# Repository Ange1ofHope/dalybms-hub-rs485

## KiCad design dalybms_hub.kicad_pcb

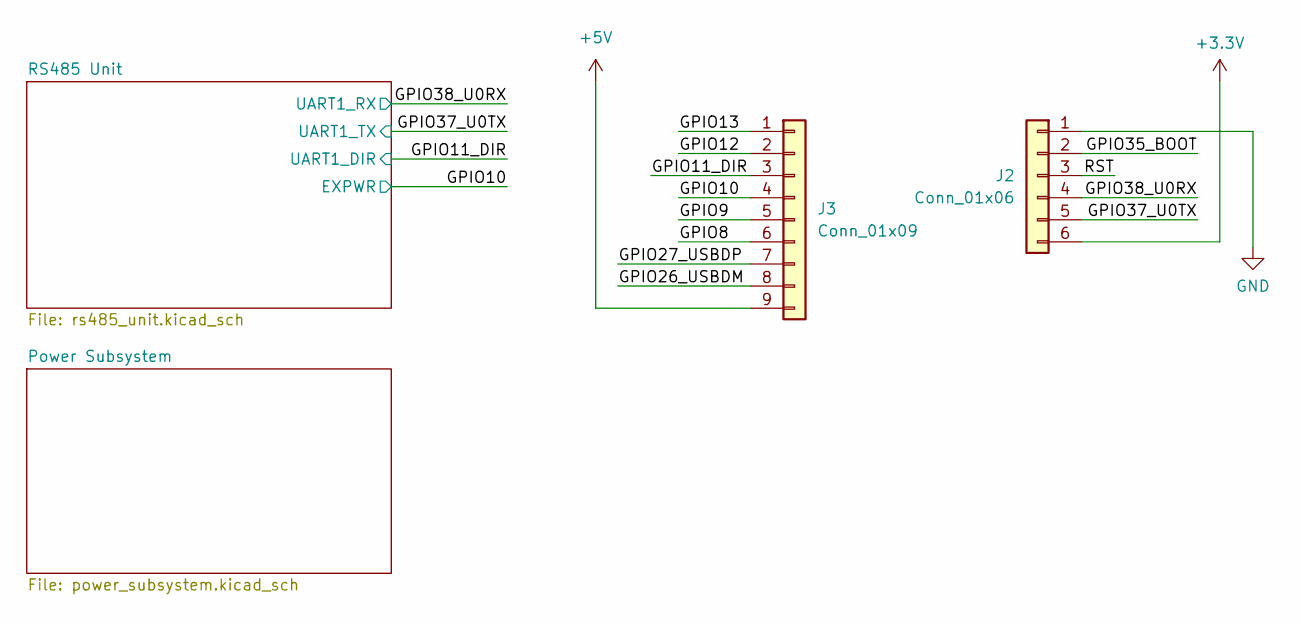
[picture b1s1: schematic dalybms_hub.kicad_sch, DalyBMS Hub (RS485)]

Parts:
J2: Conn_01x06; PinHeader_1x06_P2.54mm_Vertical
J3: Conn_01x09; PinHeader_1x09_P2.54mm_Vertical

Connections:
+3.3V: J2.6; also elsewhere on the board
+5V: J3.9; also elsewhere on the board
/GPIO8: J3.6
/GPIO9: J3.5
/GPIO10: J3.4
/GPIO11_DIR: J3.3; also elsewhere on the board
/GPIO12: J3.2
/GPIO13: J3.1
/GPIO26_USBDM: J3.8
/GPIO27_USBDP: J3.7
/GPIO35_BOOT: J2.2
/GPIO37_U0TX: J2.5; also elsewhere on the board
/GPIO38_U0RX: J2.4; also elsewhere on the board
/RST: J2.3
GND: J2.1; also elsewhere on the board

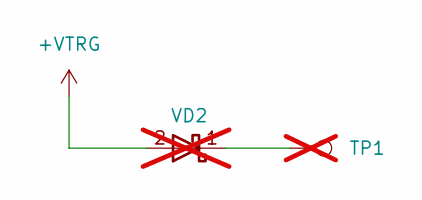
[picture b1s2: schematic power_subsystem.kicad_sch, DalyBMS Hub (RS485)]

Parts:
TP1: TestPoint; TestPoint_Pad_D1.0mm; not fitted
VD2: BAT54WS; D_SOD-323; Manufacturer Part Number BAT54WS; not fitted

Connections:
unnamed: TP1.1, VD2.1 (A)

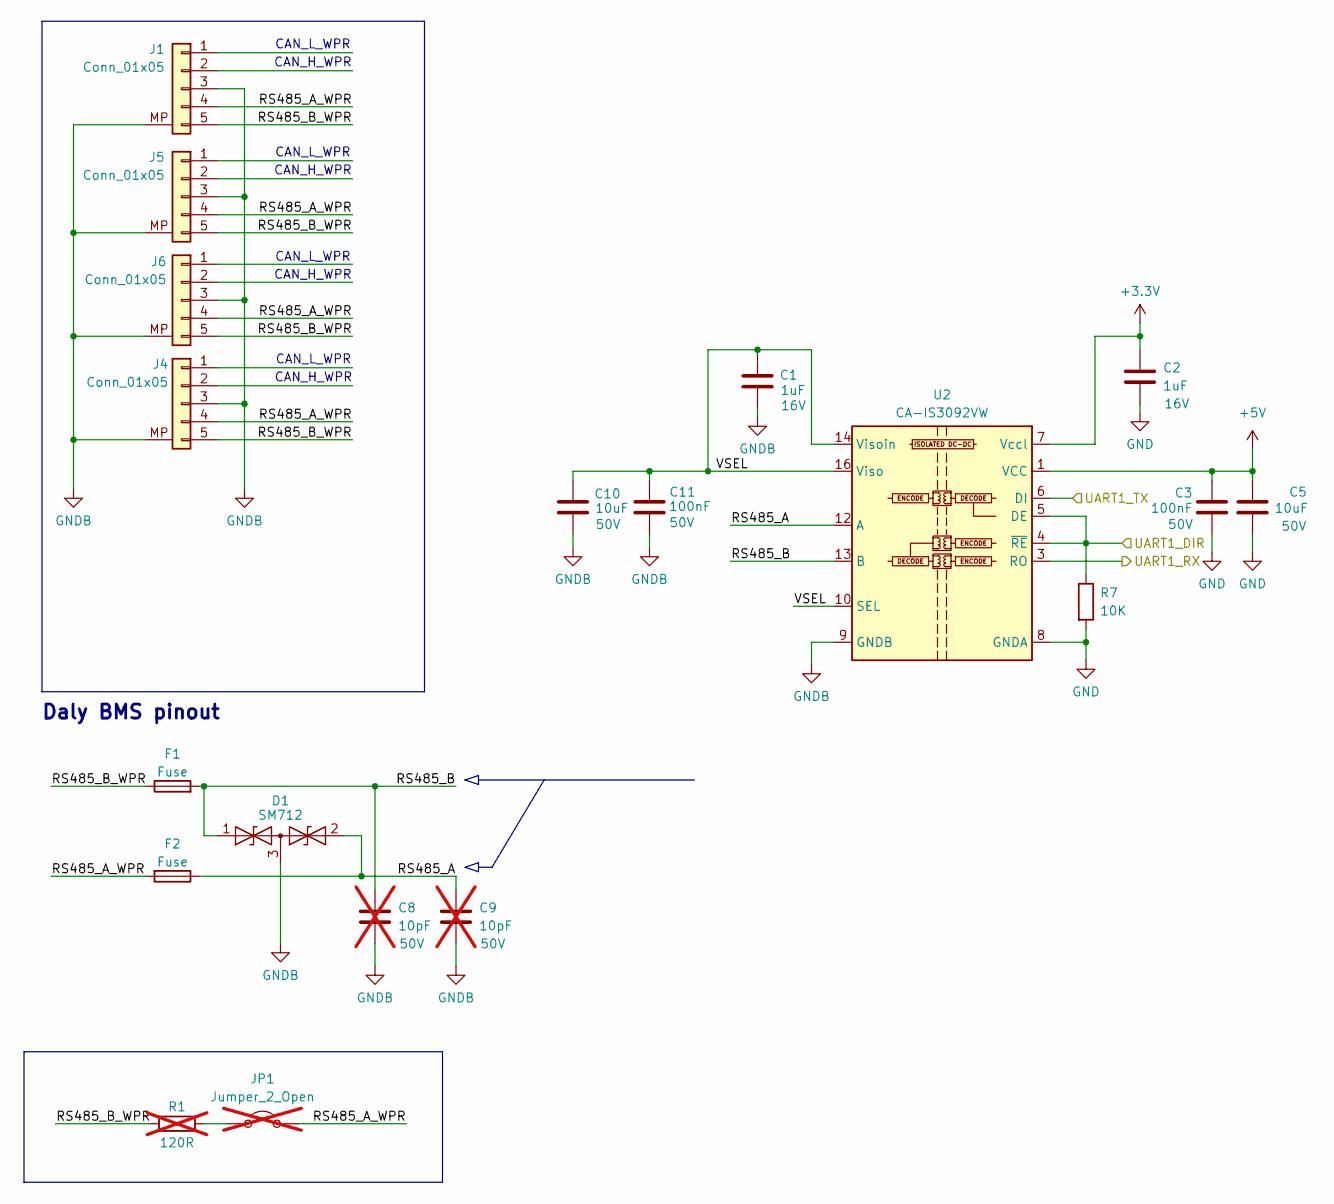
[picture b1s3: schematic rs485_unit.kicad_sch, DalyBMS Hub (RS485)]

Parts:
C1, C2: 1uF; C_0603_1608Metric; Voltage 16V
C3, C11: 100nF; C_0603_1608Metric; Voltage 50V
C5, C10: 10uF; C_0805_2012Metric; Voltage 50V
C8, C9: 10pF; C_0603_1608Metric; Voltage 50V; not fitted
D1: SM712; SOT-23
F1, F2: Fuse; Fuse_0805_2012Metric
J1, J4, J5, J6: Conn_01x05; JST_GH_SM05B-GHS-TB_1x05-1MP_P1.25mm_Horizontal
JP1: Jumper_2_Open; PinHeader_1x02_P2.00mm_Horizontal; not fitted
R1: 120R; R_0805_2012Metric; not fitted
R7: 10K; R_0603_1608Metric
U2: CA-IS3092VW; SOIC-16W_7.5x10.3mm_P1.27mm

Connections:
+3.3V: C2.1, U2.7 (Vccl); also elsewhere on the board
+5V: C3.2, C5.1, U2.1 (VCC); also elsewhere on the board
/GPIO11_DIR: R7.1, U2.4 (~RE), U2.5 (DE); also elsewhere on the board
/GPIO37_U0TX: U2.6 (DI); also elsewhere on the board
/GPIO38_U0RX: U2.3 (RO); also elsewhere on the board
/RS485 Unit/RS485_A: C9.1, D1.2 (A2), F2.1, U2.12 (A)
/RS485 Unit/RS485_A_WPR: F2.2, J1.4, J4.4, J5.4, J6.4, JP1.2 (B)
/RS485 Unit/RS485_B: C8.1, D1.1 (A1), F1.2, U2.13 (B)
/RS485 Unit/RS485_B_WPR: F1.1, J1.5, J4.5, J5.5, J6.5, R1.1
/RS485 Unit/VSEL: C1.1, C10.1, C11.1, U2.10 (SEL), U2.14 (Visoin), U2.16 (Viso)
GND: C2.2, C3.1, C5.2, R7.2, U2.2 (GNDA), U2.8 (GNDA); also elsewhere on the board
GNDB: C1.2, C8.2, C9.2, C10.2, C11.2, D1.3 (common), J1.3, J1.MP, J4.3, J4.MP, J5.3, J5.MP, J6.3, J6.MP, U2.9 (GNDB), U2.15 (GNDB)
unnamed: JP1.1 (A), R1.2

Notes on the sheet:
CAN_H_WPR
CAN_L_WPR
Daly BMS pinout

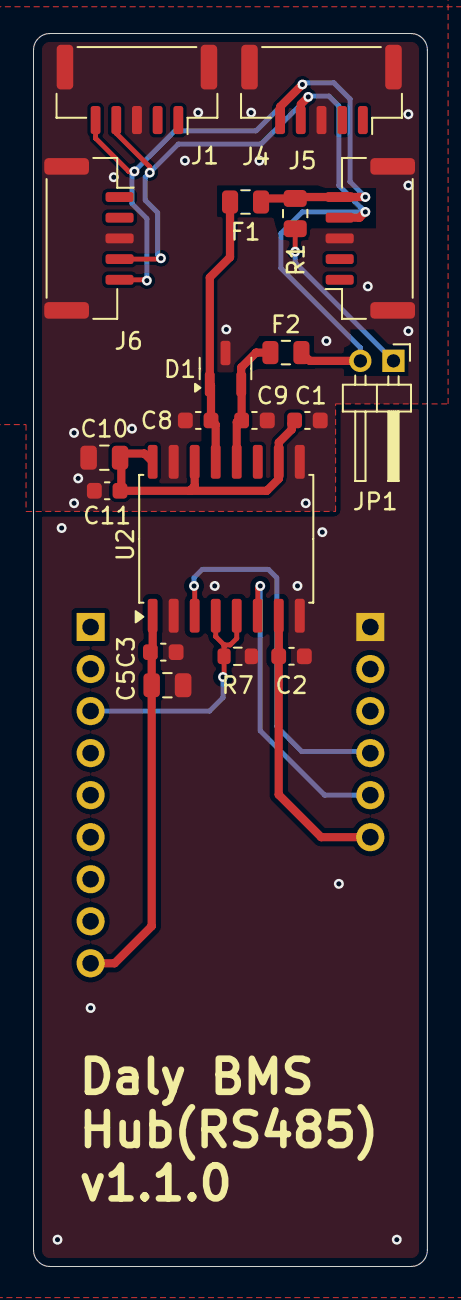
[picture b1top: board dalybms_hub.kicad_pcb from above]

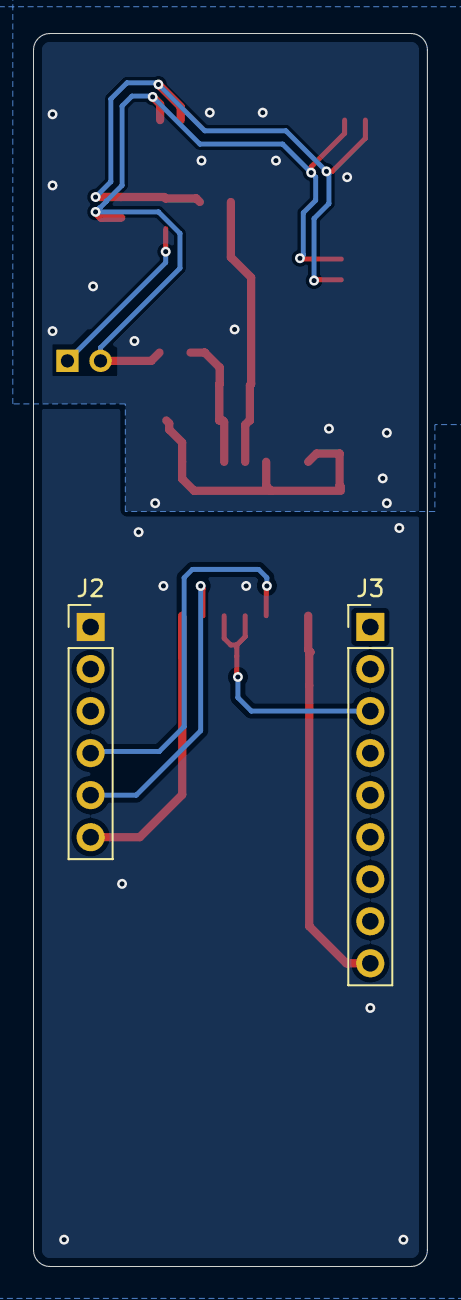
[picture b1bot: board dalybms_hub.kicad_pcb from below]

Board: 2 copper layers, 23.8 x 74.5 mm, 21 parts (2 on the bottom side), 13 nets.
